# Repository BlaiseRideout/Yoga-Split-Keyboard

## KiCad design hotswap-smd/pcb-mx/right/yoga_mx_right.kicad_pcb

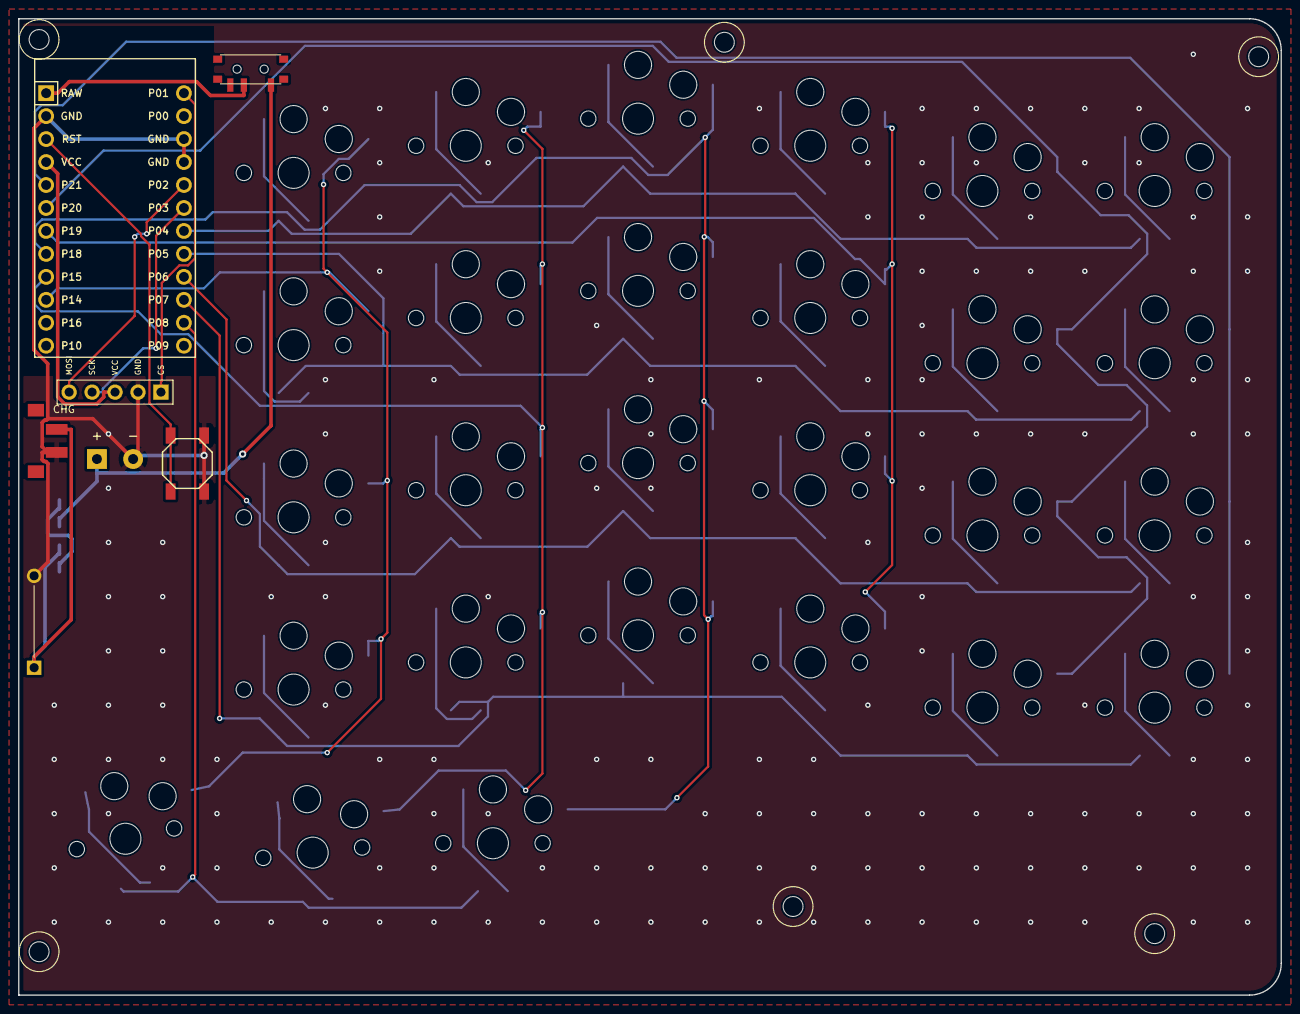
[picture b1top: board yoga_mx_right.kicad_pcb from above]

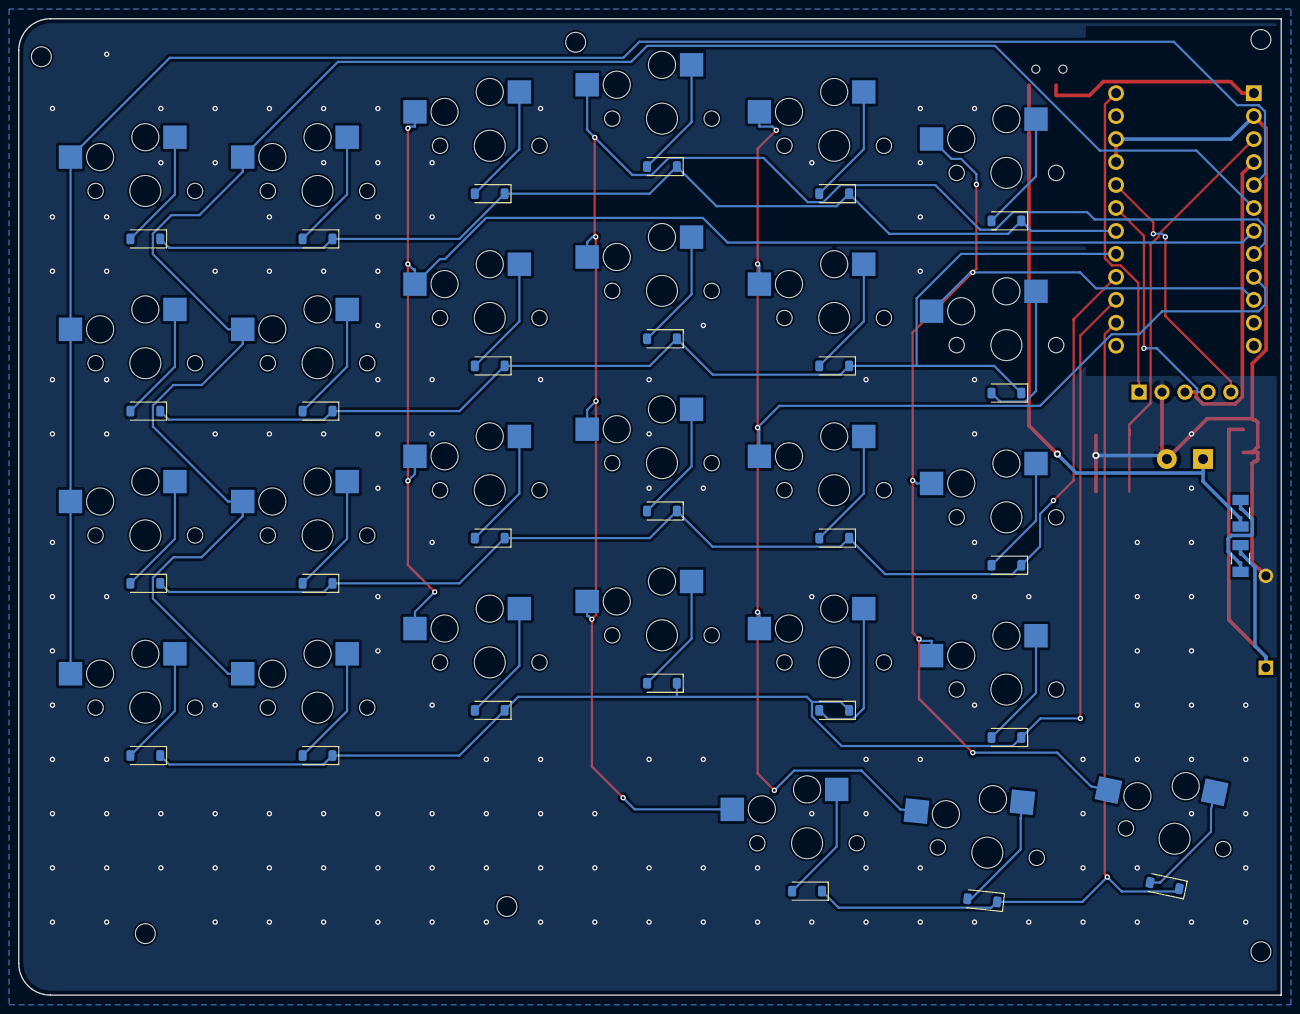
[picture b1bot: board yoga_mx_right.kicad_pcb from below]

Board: 2 copper layers, 139.7 x 108.0 mm, 69 parts (29 on the bottom side), 48 nets.

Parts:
B1: SW_TACT_ALPS_SKQGABE010
BT1: LiPo; Battery_Pads
D1, D2, D3, D4, D5, D6, D7, D8, D9, D10, D11, D12, D13, D14, D15, D16, D17, D18, D19, D20, D21, D22, D23, D24, D25, D26, D27: 1N4148W; D_SOD-123
D28: P4KE10A TVS, DO-41, band to LINK; THT2_P10.16
DISP1: nice!view; nice_view
F1: PTC 0.1A hold 1206; SMD_1206
H1, H2, H3, H4, H5, H6: M2; MountingHole_M2
J1: Pogo 2P female; Pogo_2P_RA_female
MCU1: ProMicro
R1: 10R 1206 0.25W; SMD_1206
S1, S2, S3, S4, S5, S6, S7, S8, S9, S10, S11, S12, S13, S14, S15, S16, S17, S18, S19, S20, S21, S22, S23, S24, S25, S26, S27: PG1350
SW1: MSK-12C02; SW_MSK12C02

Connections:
BAT_P: BT1.1, F1.1, SW1.1
C0: MCU1.5, S1.2, S2.2, S3.2, S4.2
C1: MCU1.6, S5.2, S6.2, S7.2, S8.2
C2: MCU1.7, S9.2, S10.2, S11.2, S12.2
C3: MCU1.8, S13.2, S14.2, S15.2, S16.2, S25.2
C4: MCU1.9, S17.2, S18.2, S19.2, S20.2, S26.2
C5: MCU1.10, S21.2, S22.2, S23.2, S24.2, S27.2
CS: DISP1.5, MCU1.13
GND: B1.2, BT1.2, D28.2, DISP1.4, J1.1, MCU1.2, MCU1.15, MCU1.16
LINK_B: D28.1, J1.2, R1.2
LINK_F: F1.2, R1.1
MOSI: DISP1.1, MCU1.17
R0: D4.1, D8.1, D12.1, D16.1, D20.1, D24.1, MCU1.19
R1: D3.1, D7.1, D11.1, D15.1, D19.1, D23.1, MCU1.20
R2: D2.1, D6.1, D10.1, D14.1, D18.1, D22.1, MCU1.21
R3: D1.1, D5.1, D9.1, D13.1, D17.1, D21.1, MCU1.22
R4: D25.1, D26.1, D27.1, MCU1.23
RAW: MCU1.1, SW1.2
RST: B1.1, MCU1.3
SCK: DISP1.2, MCU1.18
VCC: DISP1.3, MCU1.4
mirror_home_one: D26.2, S26.1
mirror_index_bottom: D17.2, S17.1
mirror_index_home: D18.2, S18.1
mirror_index_num: D20.2, S20.1
mirror_index_top: D19.2, S19.1
mirror_inner_bottom: D21.2, S21.1
mirror_inner_home: D22.2, S22.1
mirror_inner_num: D24.2, S24.1
mirror_inner_top: D23.2, S23.1
mirror_middle_bottom: D13.2, S13.1
mirror_middle_home: D14.2, S14.1
mirror_middle_num: D16.2, S16.1
mirror_middle_top: D15.2, S15.1
mirror_outer_bottom: D1.2, S1.1
mirror_outer_home: D2.2, S2.1
mirror_outer_num: D4.2, S4.1
mirror_outer_top: D3.2, S3.1
mirror_pinky_bottom: D5.2, S5.1
mirror_pinky_home: D6.2, S6.1
mirror_pinky_num: D8.2, S8.1
mirror_pinky_top: D7.2, S7.1
mirror_reachy_one: D27.2, S27.1
mirror_ring_bottom: D9.2, S9.1
mirror_ring_home: D10.2, S10.1
mirror_ring_num: D12.2, S12.1
mirror_ring_top: D11.2, S11.1
mirror_tucky_one: D25.2, S25.1
